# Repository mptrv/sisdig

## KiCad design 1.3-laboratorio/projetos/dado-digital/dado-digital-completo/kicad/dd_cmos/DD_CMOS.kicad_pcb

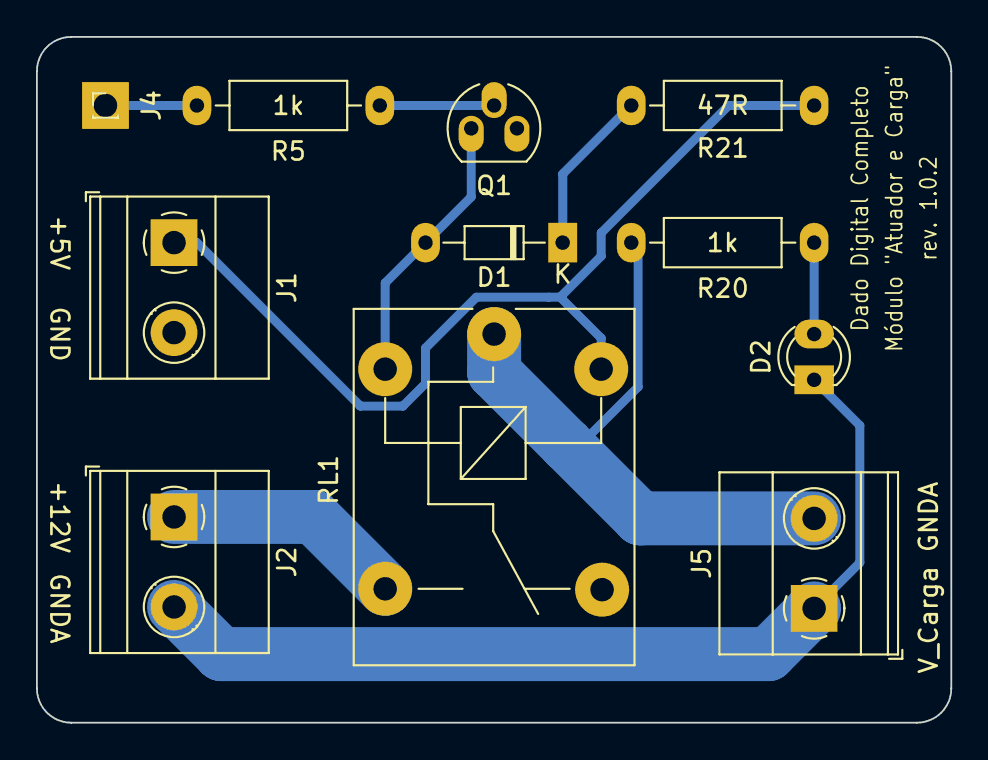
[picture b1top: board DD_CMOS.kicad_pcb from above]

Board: 2 copper layers, 50.8 x 38.1 mm, 11 parts (0 on the bottom side), 10 nets.

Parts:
D1: 1N4148; D_DO-34_SOD68_P7.62mm_Horizontal
D2: Verde; LED_D3.0mm
J1, J2, J5: Conn_01x02; TerminalBlock_Phoenix_MKDS-1,5-2_1x02_P5.00mm_Horizontal
J4: Conn_01x01; PinHeader_1x01_P1.00mm_Vertical
Q1: BC547; TO-92_HandSolder
R5, R20: 1k; R_Axial_DIN0207_L6.3mm_D2.5mm_P10.16mm_Horizontal
R21: 47R; R_Axial_DIN0207_L6.3mm_D2.5mm_P10.16mm_Horizontal
RL1: HF3FA/005-ZSTF; Relay_SPDT_SANYOU_SRD_Series_Form_C

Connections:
+12V: J2.1, RL1.14
Earth: D2.1, J2.2, J5.1
GND: J1.2, Q1.3
unnamed: D1.1, R21.2
unnamed: D1.2, Q1.1, RL1.A2
unnamed: D2.2, R20.2
unnamed: J4.1, R5.1
unnamed: J5.2, R20.1, RL1.11
unnamed: Q1.2, R5.2
VDD: J1.1, R21.1, RL1.A1

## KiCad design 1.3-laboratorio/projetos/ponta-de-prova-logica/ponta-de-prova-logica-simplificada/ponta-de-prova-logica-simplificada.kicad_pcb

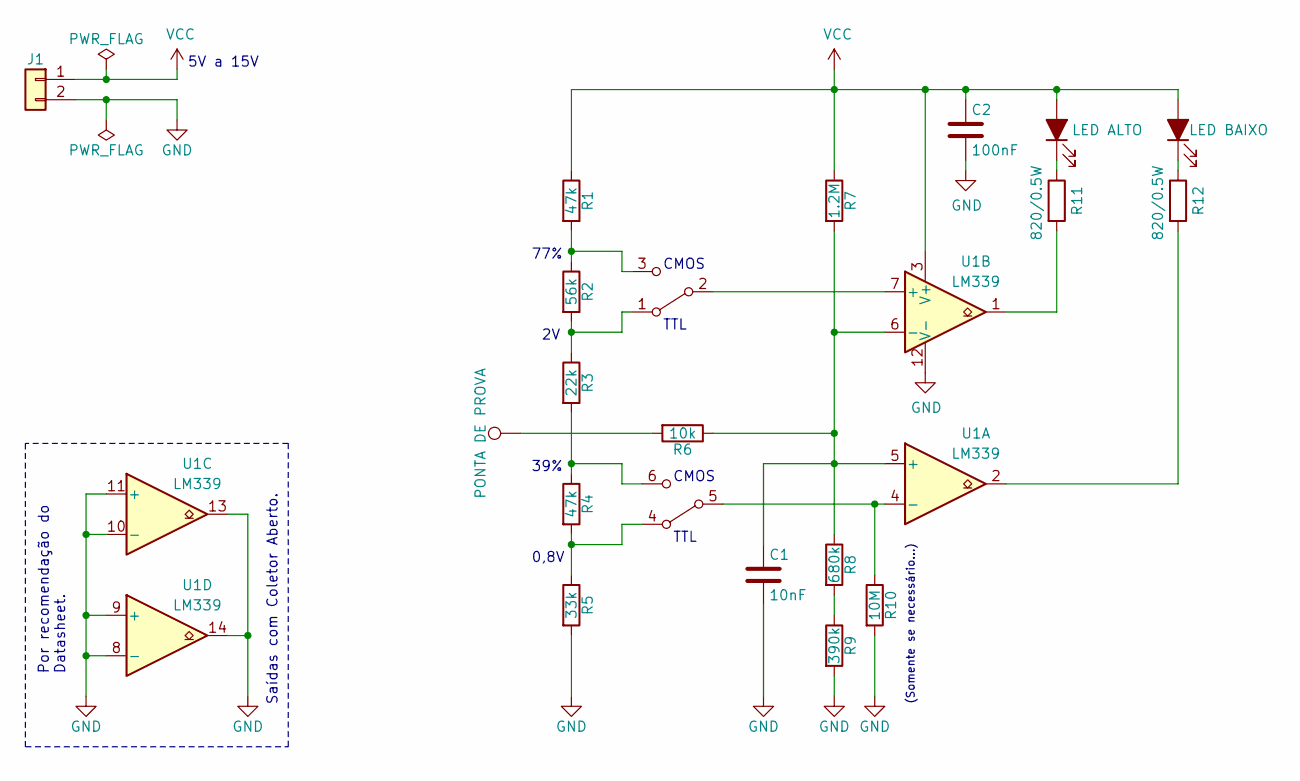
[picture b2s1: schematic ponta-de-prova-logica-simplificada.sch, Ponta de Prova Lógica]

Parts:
C1: 10nF; C_Disc_D5.0mm_W2.5mm_P5.00mm
C2: 100nF; C_Disc_D5.0mm_W2.5mm_P5.00mm
D1: LED ALTO; LED_D3.0mm
D2: LED BAIXO; LED_D3.0mm
J1: Conn_01x02; TerminalBlock_Altech_AK300-2_P5.00mm
J2: PONTA DE PROVA; SolderWirePad_1x01_Drill0.8mm
R1, R4: 47k; R_Axial_DIN0207_L6.3mm_D2.5mm_P7.62mm_Horizontal
R2: 56k; R_Axial_DIN0207_L6.3mm_D2.5mm_P7.62mm_Horizontal
R3: 22k; R_Axial_DIN0207_L6.3mm_D2.5mm_P7.62mm_Horizontal
R5: 33k; R_Axial_DIN0207_L6.3mm_D2.5mm_P7.62mm_Horizontal
R6: 10k; R_Axial_DIN0207_L6.3mm_D2.5mm_P7.62mm_Horizontal
R7: 1.2M; R_Axial_DIN0207_L6.3mm_D2.5mm_P7.62mm_Horizontal
R8: 680k; R_Axial_DIN0207_L6.3mm_D2.5mm_P7.62mm_Horizontal
R9: 390k; R_Axial_DIN0207_L6.3mm_D2.5mm_P7.62mm_Horizontal
R10: 10M; R_Axial_DIN0207_L6.3mm_D2.5mm_P7.62mm_Horizontal
R11, R12: 820/0.5W; R_Axial_DIN0207_L6.3mm_D2.5mm_P7.62mm_Horizontal
TTL1: SW_DPDT_x2; SW_CuK_JS202011CQN_DPDT_Straight
U1: LM339; DIP-14_W7.62mm_Socket_LongPads

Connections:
GND: C1.2, C2.2, J1.2, R5.2, R9.2, R10.2, U1.8 (-), U1.9 (+), U1.10 (-), U1.11 (+), U1.12 (V-), U1.13, U1.14
unnamed: C1.1, R6.1, R7.2, R8.1, U1.5 (+), U1.6 (-)
unnamed: D1.1 (K), R11.1
unnamed: D2.1 (K), R12.1
unnamed: J2.1, R6.2
unnamed 5: R1.2, R2.1, TTL1.3 (C); also elsewhere on the board
unnamed 6: R2.2, R3.1, TTL1.1 (A); also elsewhere on the board
unnamed 7: R3.2, R4.1, TTL1.6 (C); also elsewhere on the board
unnamed 8: R4.2, R5.1, TTL1.4 (A); also elsewhere on the board
unnamed: R8.2, R9.1
unnamed 10: R10.1, TTL1.5 (B), U1.4 (-); also elsewhere on the board
unnamed: R11.2, U1.1
unnamed: R12.2, U1.2
unnamed 13: TTL1.2 (B), U1.7 (+); also elsewhere on the board
VCC: C2.1, D1.2 (A), D2.2 (A), J1.1, R1.1, R7.1, U1.3 (V+)

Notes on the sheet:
0,8V
39%
77%
CMOS
TTL
Saídas com Coletor Aberto.
Por recomendação do Datasheet.
(Somente se necessário...)
5V a 15V

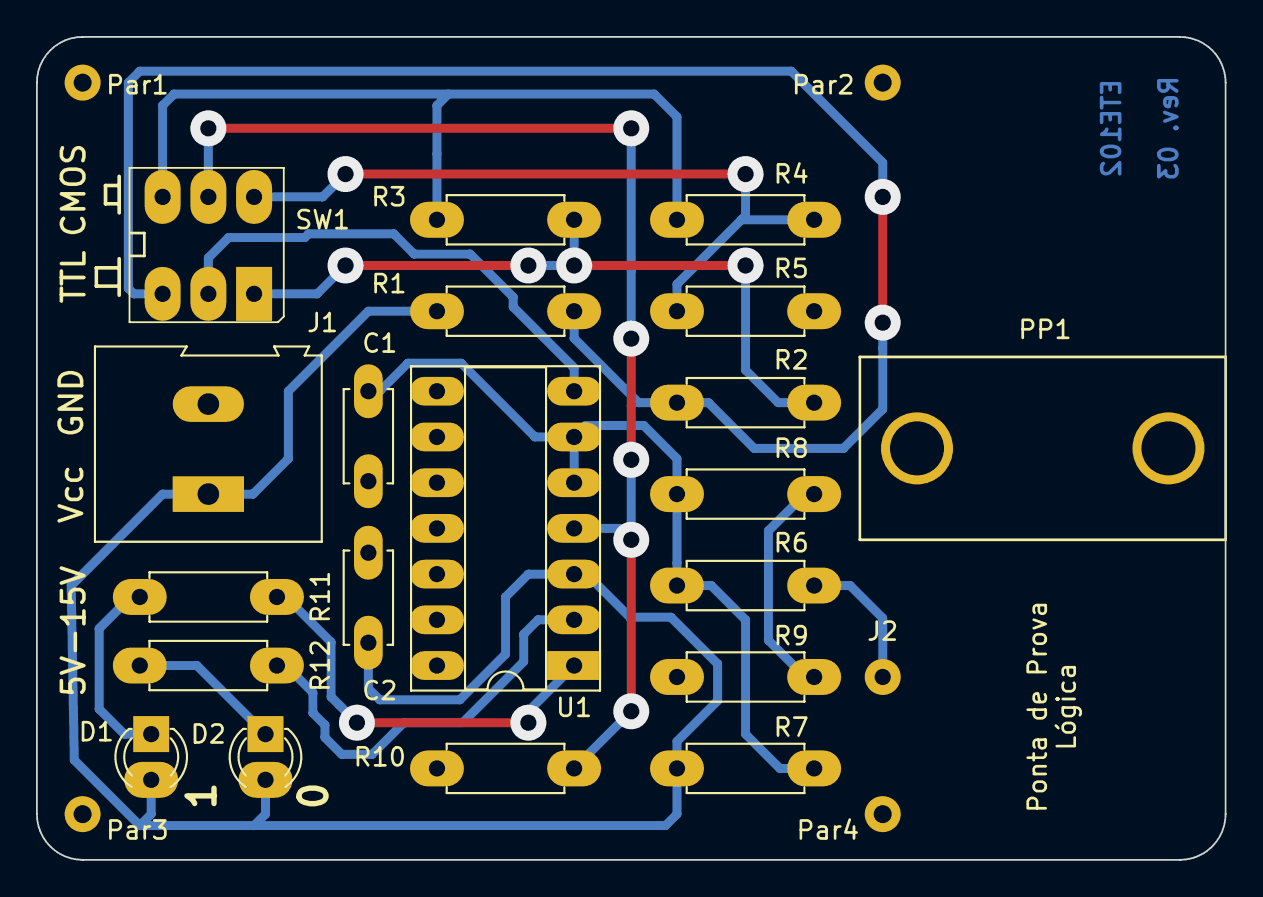
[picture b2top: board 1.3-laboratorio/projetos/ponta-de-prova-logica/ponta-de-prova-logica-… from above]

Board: 2 copper layers, 66.0 x 45.7 mm, 25 parts (0 on the bottom side), 15 nets.

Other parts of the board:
PP1: ponta-de-prova-fixacao-20mm-x-10mm-x-10mm
Par1, Par2, Par3, Par4: MountingHole_1mm_M1_DIN965_Pad; MountingHole_2.2mm_M2_DIN965_Pad
SW1: SW_DPDT_x2; Switch_Slide_JS202011SCQN

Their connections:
unnamed 5: SW1.3; also elsewhere on the board
unnamed 6: SW1.1; also elsewhere on the board
unnamed 7: SW1.6; also elsewhere on the board
unnamed 8: SW1.4; also elsewhere on the board
unnamed 10: SW1.5; also elsewhere on the board
unnamed 13: SW1.2; also elsewhere on the board

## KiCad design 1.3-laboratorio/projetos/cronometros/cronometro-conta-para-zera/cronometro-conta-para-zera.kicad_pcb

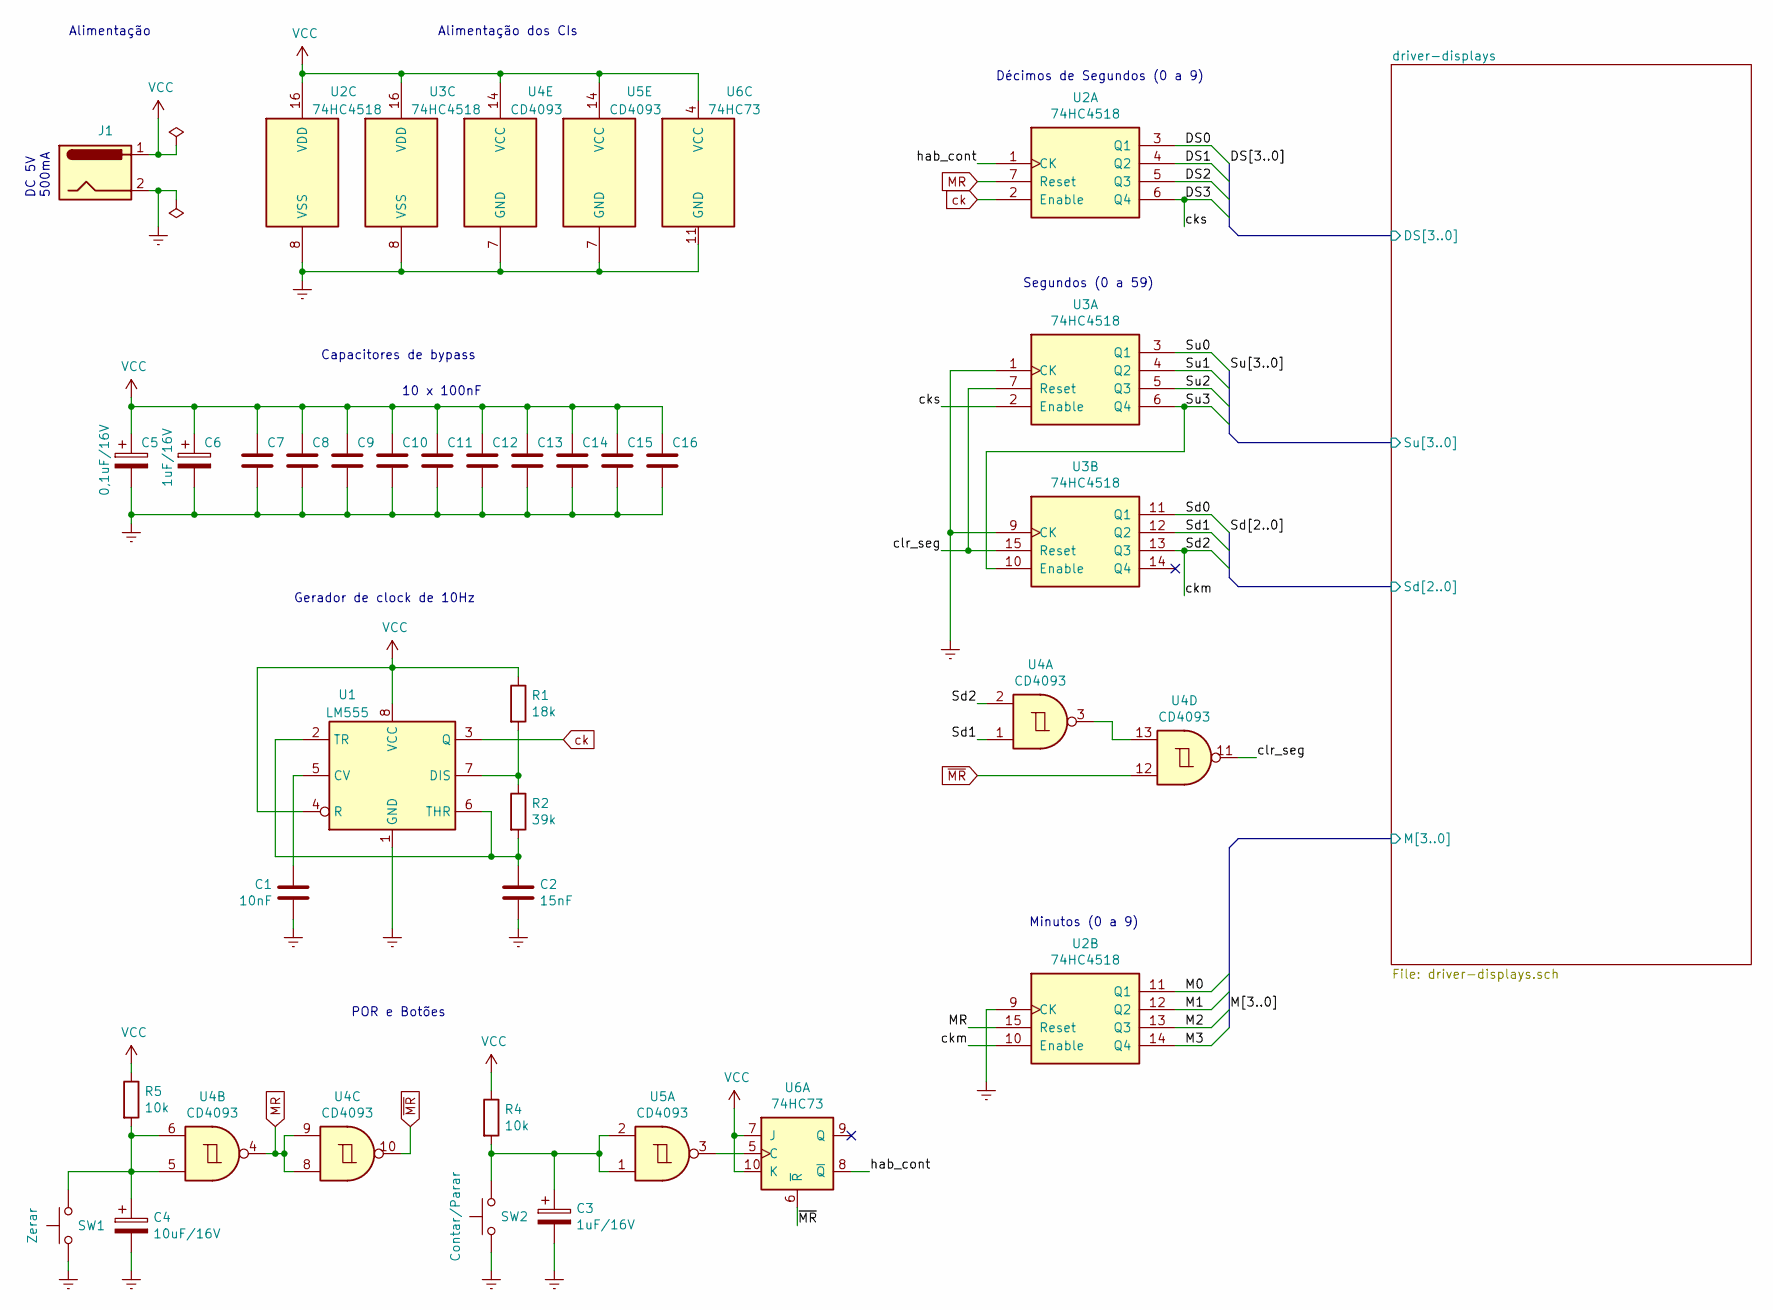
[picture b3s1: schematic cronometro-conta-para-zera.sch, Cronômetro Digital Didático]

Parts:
C1: 10nF
C2: 15nF
C3, C6: 1uF/16V
C4: 10uF/16V
C5: 0,1uF/16V
C7, C8, C9, C10, C11, C12, C13, C14, C15, C16: 100nF
J1: Barrel_Jack_Switch; BarrelJack_CUI_PJ-063AH_Horizontal
R1: 18k
R2: 39k
R4, R5: 10k
SW1, SW2: SW_Push
U1: LM555; DIP-8_W7.62mm
U2, U3: 74HC4518
U4, U5: CD4093
U6: 74HC73

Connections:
/DS0: U2.3 (Q1); also elsewhere on the board
/DS1: U2.4 (Q2); also elsewhere on the board
/DS2: U2.5 (Q3); also elsewhere on the board
/M0: U3.11 (Q1); also elsewhere on the board
/M3: U3.14 (Q4); also elsewhere on the board
/Sd0: U3.3 (Q1); also elsewhere on the board
/Su0: U2.11 (Q1); also elsewhere on the board
/Su1: U2.12 (Q2); also elsewhere on the board
/Su2: U2.13 (Q3); also elsewhere on the board
/hab_cont: U2.1 (CK), U6.8 (~Q)
Earth: C1.2, C2.2, C3.2, C4.2, C5.2, C6.2, C7.2, C8.2, C9.2, C10.2, C11.2, C12.2, C13.2, C14.2, C15.2, C16.2, J1.2, SW1.1, SW2.1, U1.1 (GND), U2.8 (VSS), U2.9 (CK), U3.1 (CK), U3.8 (VSS), U3.9 (CK), U4.7 (GND), U5.7 (GND), U6.11 (GND); also elsewhere on the board
unnamed: C1.1, U1.5 (CV)
unnamed: C2.1, R2.2, U1.2 (TR), U1.6 (THR)
unnamed: C3.1, R4.2, SW2.2, U5.1, U5.2
unnamed: C4.1, R5.2, SW1.2, U4.5, U4.6
unnamed: R1.2, R2.1, U1.7 (DIS)
unnamed: U4.3, U4.13
unnamed: U5.3, U6.5 (C)
VCC: C5.1, C6.1, C7.1, C8.1, C9.1, C10.1, C11.1, C12.1, C13.1, C14.1, C15.1, C16.1, J1.1, R1.1, R4.1, R5.1, U1.4 (R), U1.8 (VCC), U2.16 (VDD), U3.16 (VDD), U4.14 (VCC), U5.14 (VCC), U6.4 (VCC), U6.7 (J), U6.10 (K); also elsewhere on the board
ck: U1.3 (Q), U2.2 (Enable)
~MR: U4.10, U4.12, U6.6 (~R)

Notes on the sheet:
DC 5V 500mA
Gerador de clock de 10Hz
Décimos de Segundos (0 a 9)
Segundos (0 a 59)
Minutos (0 a 9)
POR e Botões
Capacitores de bypass
Alimentação dos CIs
10 x 100nF
Alimentação

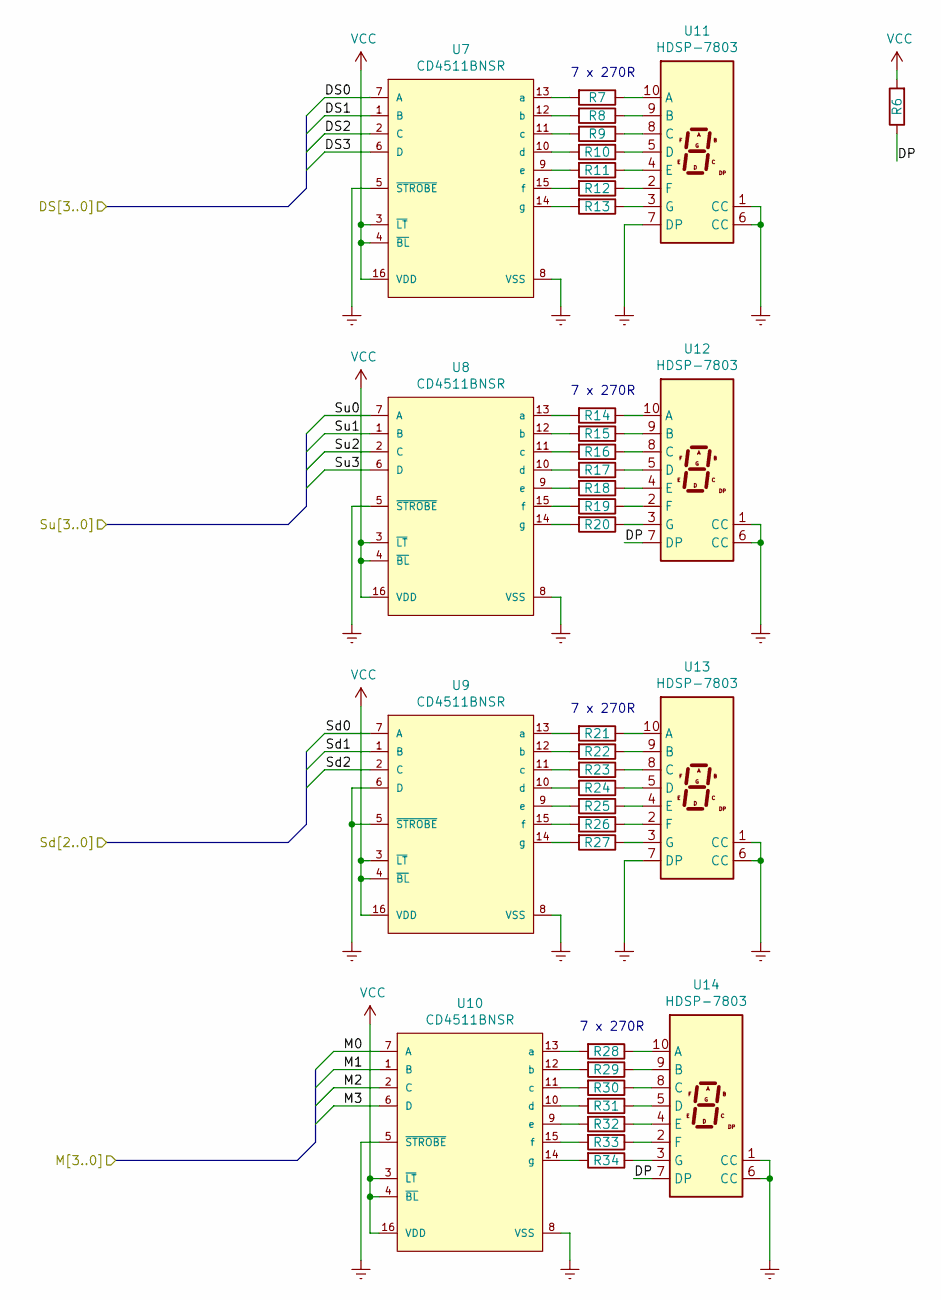
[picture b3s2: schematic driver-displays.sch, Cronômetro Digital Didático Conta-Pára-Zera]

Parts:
R6, R7, R8, R9, R10, R11, R12, R13, R14, R15, R16, R17, R18, R19, R20, R21, R22, R23, R24, R25, R26, R27, R28, R29, R30, R31, R32, R33, R34: 270R; R_Axial_DIN0204_L3.6mm_D1.6mm_P7.62mm_Horizontal
U7, U8, U9, U10: CD4511BNSR; DIP-16_W7.62mm_Socket_LongPads; Rating Military
U11, U12, U13, U14: HDSP-7803; HDSP-7801

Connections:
/DS0: U7.7 (A); also elsewhere on the board
/DS1: U7.1 (B); also elsewhere on the board
/DS2: U7.2 (C); also elsewhere on the board
/M0: U10.7 (A); also elsewhere on the board
/M3: U10.6 (D); also elsewhere on the board
/Sd0: U9.7 (A); also elsewhere on the board
/Su0: U8.7 (A); also elsewhere on the board
/Su1: U8.1 (B); also elsewhere on the board
/Su2: U8.2 (C); also elsewhere on the board
/driver-displays/DP: R6.1, U12.7 (DP), U14.7 (DP)
Earth: U7.5 (~STROBE~), U7.8 (VSS), U8.5 (~STROBE~), U8.8 (VSS), U9.5 (~STROBE~), U9.6 (D), U9.8 (VSS), U10.5 (~STROBE~), U10.8 (VSS), U11.1 (CC), U11.6 (CC), U11.7 (DP), U12.1 (CC), U12.6 (CC), U13.1 (CC), U13.6 (CC), U13.7 (DP), U14.1 (CC), U14.6 (CC); also elsewhere on the board
unnamed: R7.1, U11.10 (A)
unnamed: R7.2, U7.13 (a)
unnamed: R8.1, U11.9 (B)
unnamed: R8.2, U7.12 (b)
unnamed: R9.1, U11.8 (C)
unnamed: R9.2, U7.11 (c)
unnamed: R10.1, U11.5 (D)
unnamed: R10.2, U7.10 (d)
unnamed: R11.1, U11.4 (E)
unnamed: R11.2, U7.9 (e)
unnamed: R12.1, U11.2 (F)
unnamed: R12.2, U7.15 (f)
unnamed: R13.1, U11.3 (G)
unnamed: R13.2, U7.14 (g)
unnamed: R14.1, U12.10 (A)
unnamed: R14.2, U8.13 (a)
unnamed: R15.1, U12.9 (B)
unnamed: R15.2, U8.12 (b)
unnamed: R16.1, U12.8 (C)
unnamed: R16.2, U8.11 (c)
unnamed: R17.1, U12.5 (D)
unnamed: R17.2, U8.10 (d)
unnamed: R18.1, U12.4 (E)
unnamed: R18.2, U8.9 (e)
unnamed: R19.1, U12.2 (F)
unnamed: R19.2, U8.15 (f)
unnamed: R20.1, U12.3 (G)
unnamed: R20.2, U8.14 (g)
unnamed: R21.1, U13.10 (A)
unnamed: R21.2, U9.13 (a)
unnamed: R22.1, U13.9 (B)
unnamed: R22.2, U9.12 (b)
unnamed: R23.1, U13.8 (C)
unnamed: R23.2, U9.11 (c)
unnamed: R24.1, U13.5 (D)
unnamed: R24.2, U9.10 (d)
unnamed: R25.1, U13.4 (E)
unnamed: R25.2, U9.9 (e)
unnamed: R26.1, U13.2 (F)
unnamed: R26.2, U9.15 (f)
unnamed: R27.1, U13.3 (G)
unnamed: R27.2, U9.14 (g)
unnamed: R28.1, U14.10 (A)
unnamed: R28.2, U10.13 (a)
unnamed: R29.1, U14.9 (B)
unnamed: R29.2, U10.12 (b)
unnamed: R30.1, U14.8 (C)
unnamed: R30.2, U10.11 (c)
unnamed: R31.1, U14.5 (D)
unnamed: R31.2, U10.10 (d)
unnamed: R32.1, U14.4 (E)
unnamed: R32.2, U10.9 (e)
unnamed: R33.1, U14.2 (F)
unnamed: R33.2, U10.15 (f)
unnamed: R34.1, U14.3 (G)
unnamed: R34.2, U10.14 (g)
VCC: R6.2, U7.3 (~LT~), U7.4 (~BL~), U7.16 (VDD), U8.3 (~LT~), U8.4 (~BL~), U8.16 (VDD), U9.3 (~LT~), U9.4 (~BL~), U9.16 (VDD), U10.3 (~LT~), U10.4 (~BL~), U10.16 (VDD); also elsewhere on the board

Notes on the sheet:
7 x 270R

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
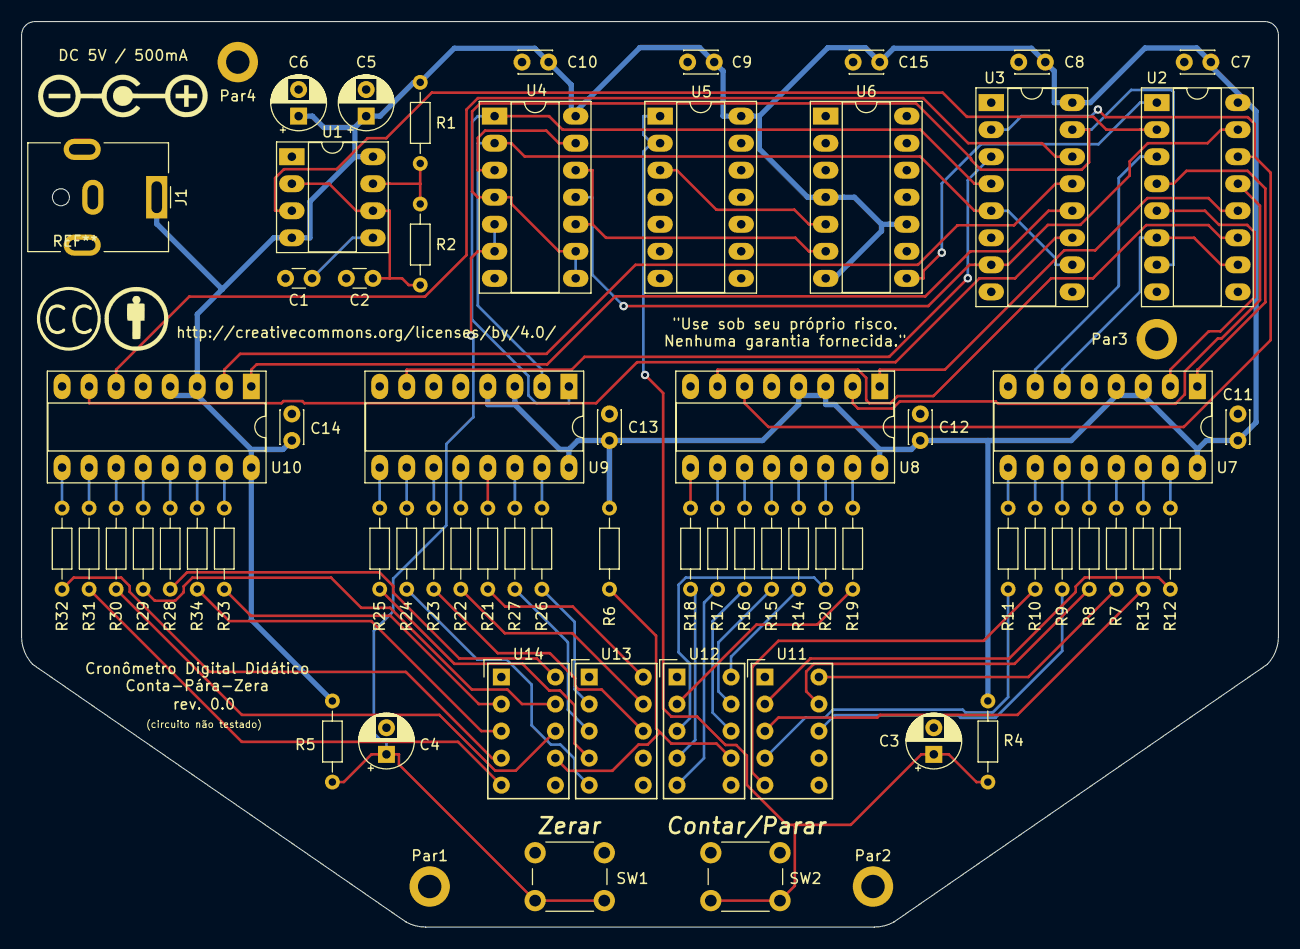
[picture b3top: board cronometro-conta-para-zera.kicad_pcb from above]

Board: 2 copper layers, 118.1 x 85.1 mm, 69 parts (0 on the bottom side), 86 nets.

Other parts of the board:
Par1, Par2, Par3, Par4: MountingHole_2.2mm_M2_DIN965_Pad

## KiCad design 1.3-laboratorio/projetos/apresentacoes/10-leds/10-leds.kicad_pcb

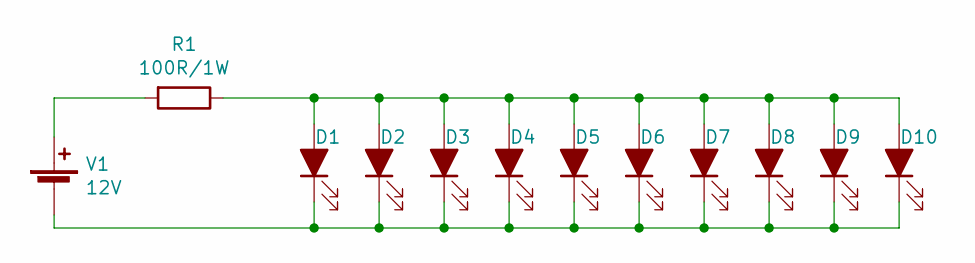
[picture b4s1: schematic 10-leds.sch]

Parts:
D1, D2, D3, D4, D5, D6, D7, D8, D9, D10: LED_ALT; LED_D5.0mm
R1: 100R/1W; R_Axial_DIN0204_L3.6mm_D1.6mm_P5.08mm_Horizontal
V1: 12V; TerminalBlock_Phoenix_MKDS-1,5-2-5.08_1x02_P5.08mm_Horizont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

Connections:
unnamed: D1.1 (K), D2.1 (K), D3.1 (K), D4.1 (K), D5.1 (K), D6.1 (K), D7.1 (K), D8.1 (K), D9.1 (K), D10.1 (K), V1.2 (-)
unnamed: D1.2 (A), D2.2 (A), D3.2 (A), D4.2 (A), D5.2 (A), D6.2 (A), D7.2 (A), D8.2 (A), D9.2 (A), D10.2 (A), R1.1
unnamed: R1.2, V1.1 (+)

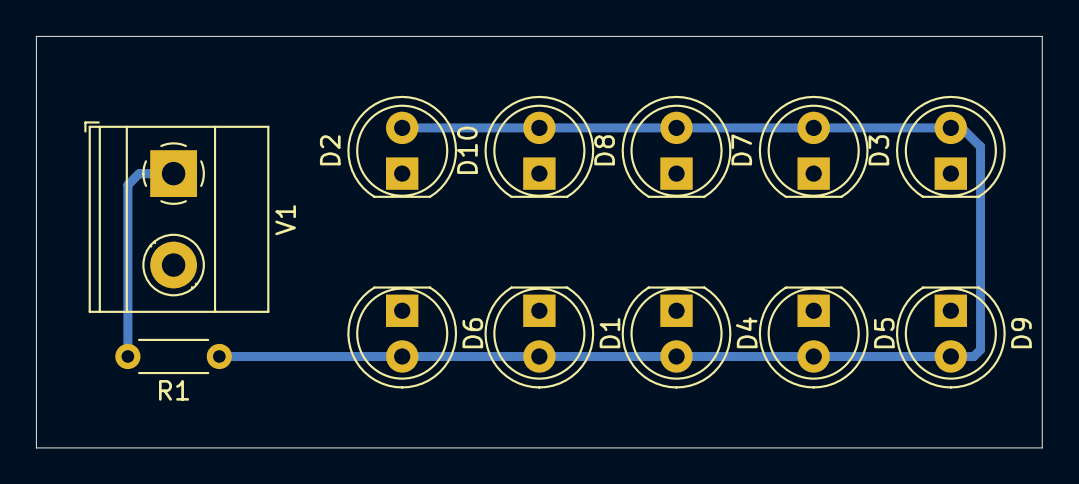
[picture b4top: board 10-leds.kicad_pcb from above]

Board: 2 copper layers, 55.9 x 22.9 mm, 12 parts (0 on the bottom side), 3 nets.

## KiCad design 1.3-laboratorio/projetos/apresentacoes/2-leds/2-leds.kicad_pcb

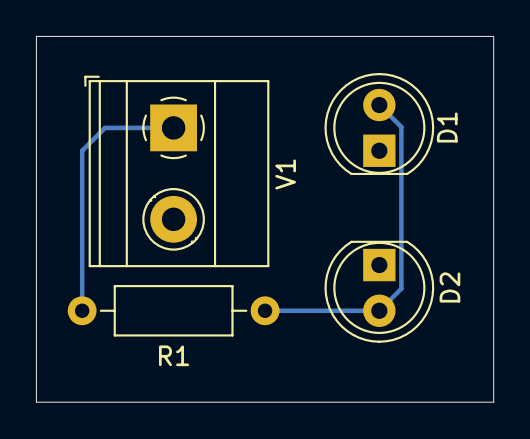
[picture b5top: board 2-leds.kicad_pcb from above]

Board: 2 copper layers, 25.4 x 20.3 mm, 4 parts (0 on the bottom side), 3 nets.

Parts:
D1, D2: LED_ALT; LED_D5.0mm
R1: 470R/0,5W; R_Axial_DIN0207_L6.3mm_D2.5mm_P10.16mm_Horizontal
V1: 12V; TerminalBlock_Phoenix_MKDS-1,5-2-5.08_1x02_P5.08mm_Horizont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

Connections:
/gnd: D1.1, D2.1, V1.2
unnamed: D1.2, D2.2, R1.2
unnamed: R1.1, V1.1

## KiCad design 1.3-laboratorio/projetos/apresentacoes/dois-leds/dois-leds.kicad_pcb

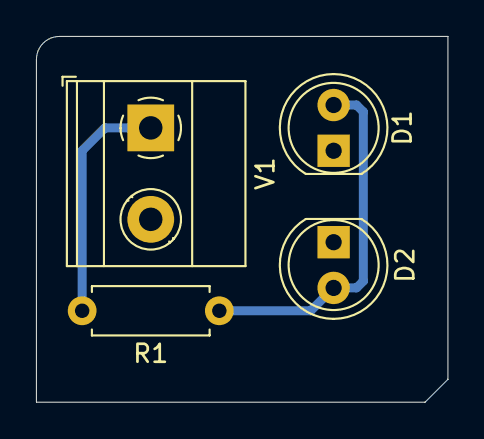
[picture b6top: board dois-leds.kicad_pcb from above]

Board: 2 copper layers, 22.9 x 20.3 mm, 4 parts (0 on the bottom side), 3 nets.

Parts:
D1, D2: LED_ALT; LED_D5.0mm
R1: 470R/0,5W; R_Axial_DIN0207_L6.3mm_D2.5mm_P7.62mm_Horizontal
V1: 12V; TerminalBlock_Phoenix_MKDS-1,5-2-5.08_1x02_P5.08mm_Horizont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

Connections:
/gnd: D1.1, D2.1, V1.2
unnamed: D1.2, D2.2, R1.1
unnamed: R1.2, V1.1

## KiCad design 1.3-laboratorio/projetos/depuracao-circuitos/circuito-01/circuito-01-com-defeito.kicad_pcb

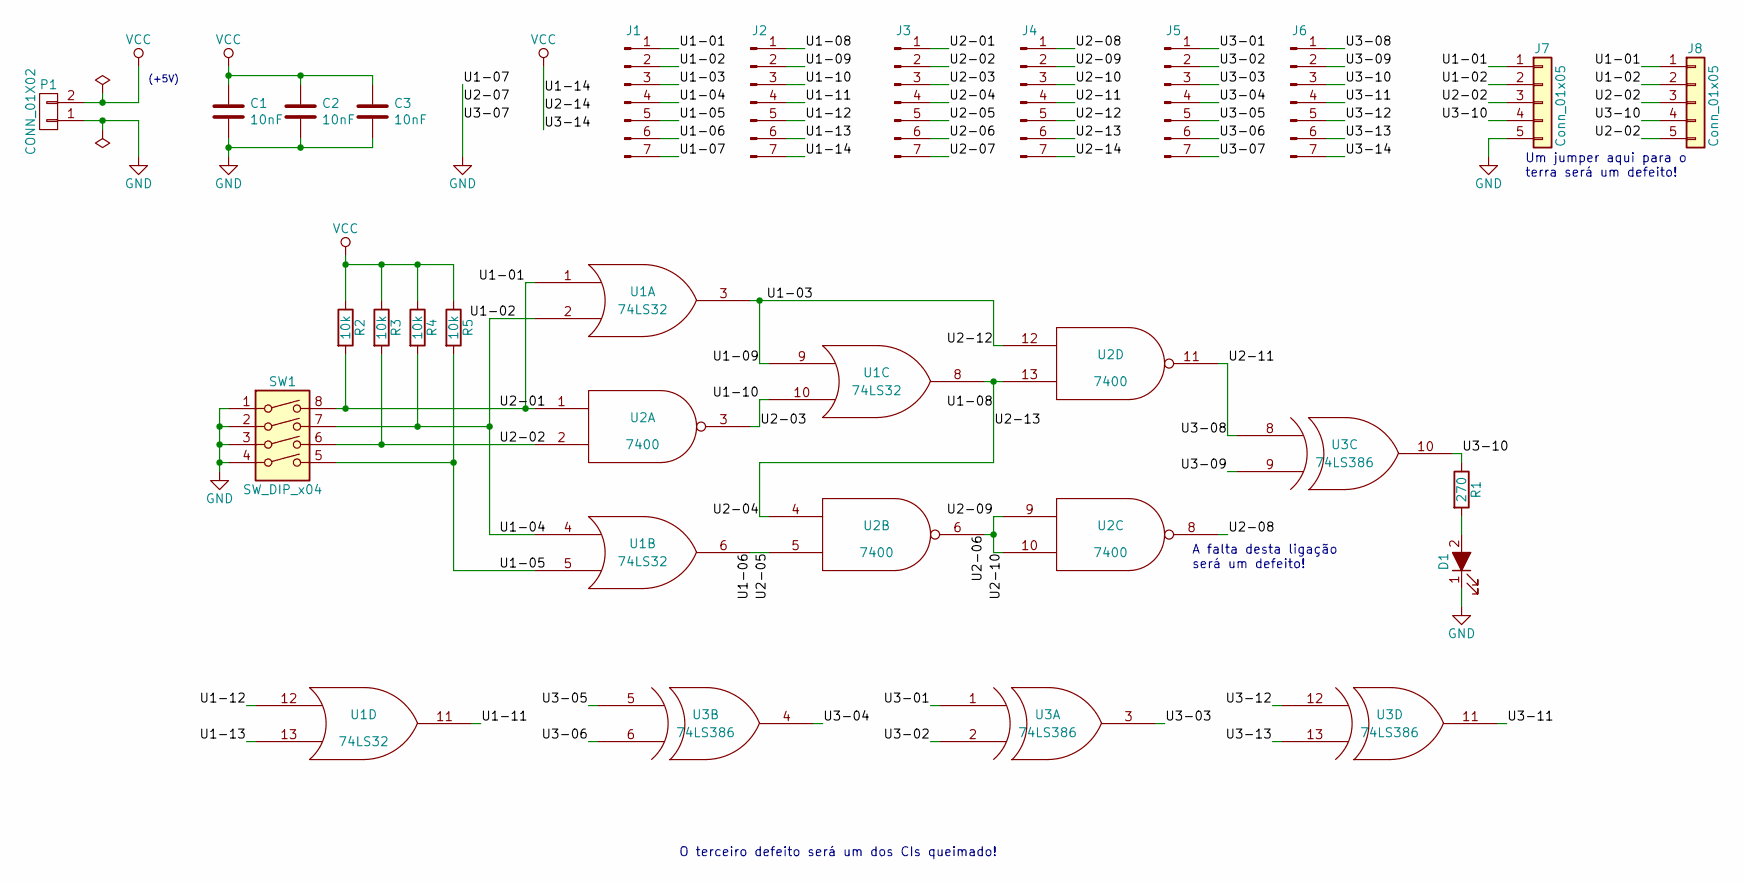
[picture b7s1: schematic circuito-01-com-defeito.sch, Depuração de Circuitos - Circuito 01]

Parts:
C1, C2, C3: 10nF; C_Disc_D5.0mm_W2.5mm_P5.00mm
D1: LED_ALT; LED_D5.0mm
J1, J2, J3, J4, J5, J6: Conn_01x07_Male; PinHeader_1x07_P2.54mm_Vertical
J7, J8: Conn_01x05; PinSocket_1x05_P2.54mm_Vertical
P1: CONN_01X02; Altech_AK300_1x02_P5.00mm_45-Degree
R1: 270; R_Axial_DIN0207_L6.3mm_D2.5mm_P10.16mm_Horizontal
R2, R3, R4, R5: 10k; R_Axial_DIN0207_L6.3mm_D2.5mm_P10.16mm_Horizontal
SW1: SW_DIP_x04; SW_DIP_SPSTx04_Slide_9.78x12.34mm_W7.62mm_P2.54mm
U1: 74LS32; DIP-14_W7.62mm_Socket_LongPads
U2: 7400; DIP-14_W7.62mm_Socket_LongPads
U3: 74LS386; DIP-14_W7.62mm_Socket_LongPads

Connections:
/U1-01: J1.1, J3.1, J7.1, J8.1, R2.2, SW1.8, U1.1, U2.1
/U1-02: J1.2, J1.4, J7.2, J8.2, R4.2, SW1.7, U1.2, U1.4
/U1-03: J1.3, J2.2, J4.5, U1.3, U1.9, U2.12
/U1-05: J1.5, R5.2, SW1.5, U1.5
/U1-06: J1.6, J3.5, U1.6, U2.5
/U1-08: J2.1, J3.4, J4.6, U1.8, U2.4, U2.13
/U1-10: J2.3, J3.3, U1.10, U2.3
/U1-11: J2.4, U1.11
/U1-12: J2.5, U1.12
/U1-13: J2.6, U1.13
/U2-02: J3.2, J7.3, J8.3, J8.5, R3.2, SW1.6, U2.2
/U2-06: J3.6, J4.2, J4.3, U2.6, U2.9, U2.10
/U2-08: J4.1, U2.8
/U2-11: J4.4, J6.1, U2.11, U3.8
/U3-01: J5.1, U3.1
/U3-02: J5.2, U3.2
/U3-03: J5.3, U3.3
/U3-04: J5.4, U3.4
/U3-05: J5.5, U3.5
/U3-06: J5.6, U3.6
/U3-09: J6.2, U3.9
/U3-10: J6.3, J7.4, J8.4, R1.1, U3.10
/U3-11: J6.4, U3.11
/U3-12: J6.5, U3.12
/U3-13: J6.6, U3.13
GND: C1.2, C2.2, C3.2, D1.1 (K), J1.7, J3.7, J5.7, J7.5, P1.1, SW1.1, SW1.2, SW1.3, SW1.4, U1.7 (GND), U2.7 (GND), U3.7 (GND)
unnamed: D1.2 (A), R1.2
VCC: C1.1, C2.1, C3.1, J2.7, J4.7, J6.7, P1.2, R2.1, R3.1, R4.1, R5.1, U1.14 (VCC), U2.14 (VCC), U3.14 (VCC)

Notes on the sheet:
(+5V)
Um jumper aqui para o terra será um defeito!
A falta desta ligação será um defeito!
O terceiro defeito será um dos CIs queimado!

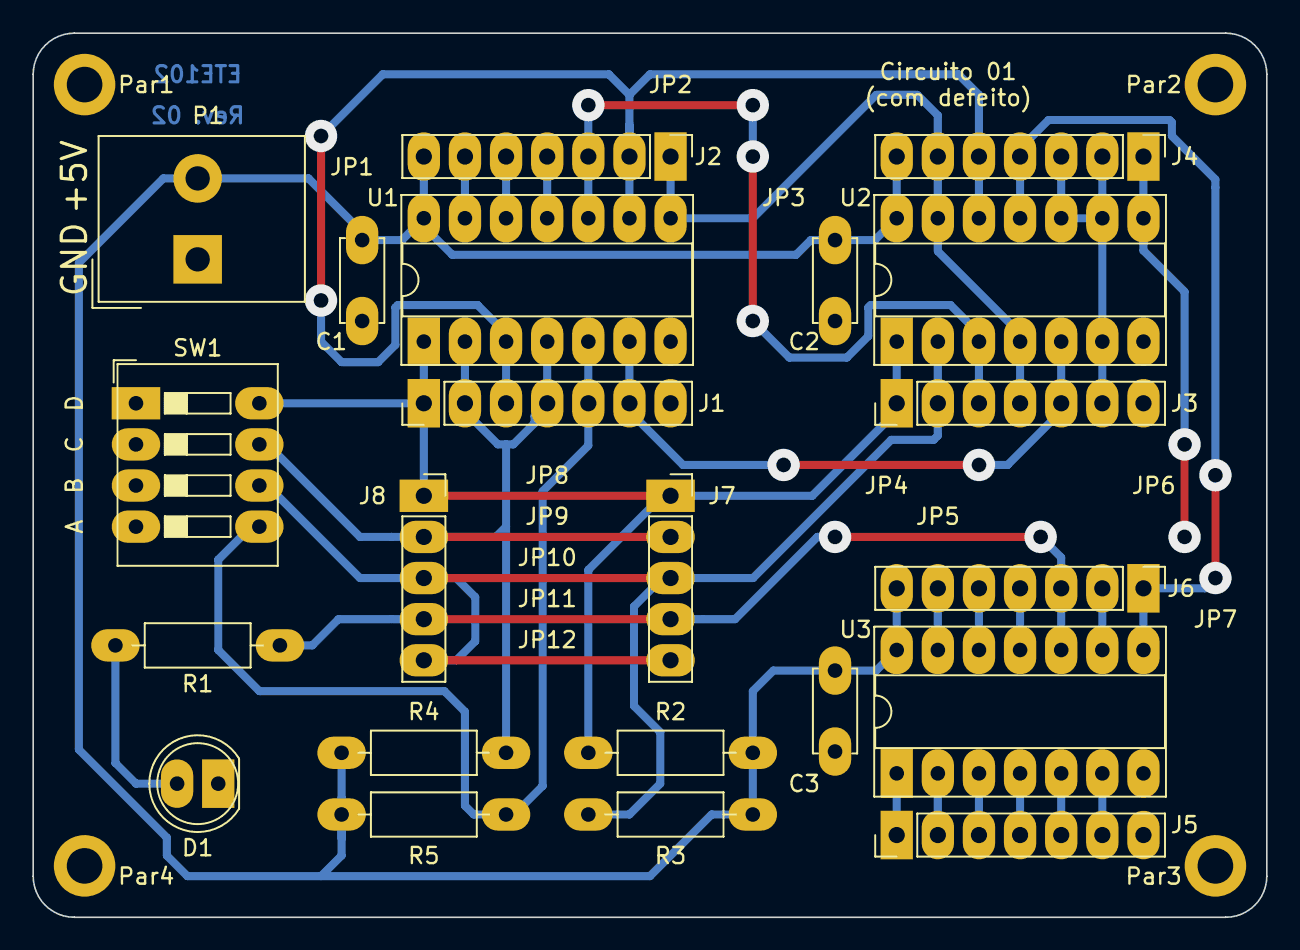
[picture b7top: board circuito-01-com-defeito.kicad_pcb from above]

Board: 2 copper layers, 76.2 x 54.6 mm, 26 parts (0 on the bottom side), 28 nets.

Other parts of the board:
Par1, Par2, Par3, Par4: MountingHole_2.2mm_M2_ISO14580_Pad

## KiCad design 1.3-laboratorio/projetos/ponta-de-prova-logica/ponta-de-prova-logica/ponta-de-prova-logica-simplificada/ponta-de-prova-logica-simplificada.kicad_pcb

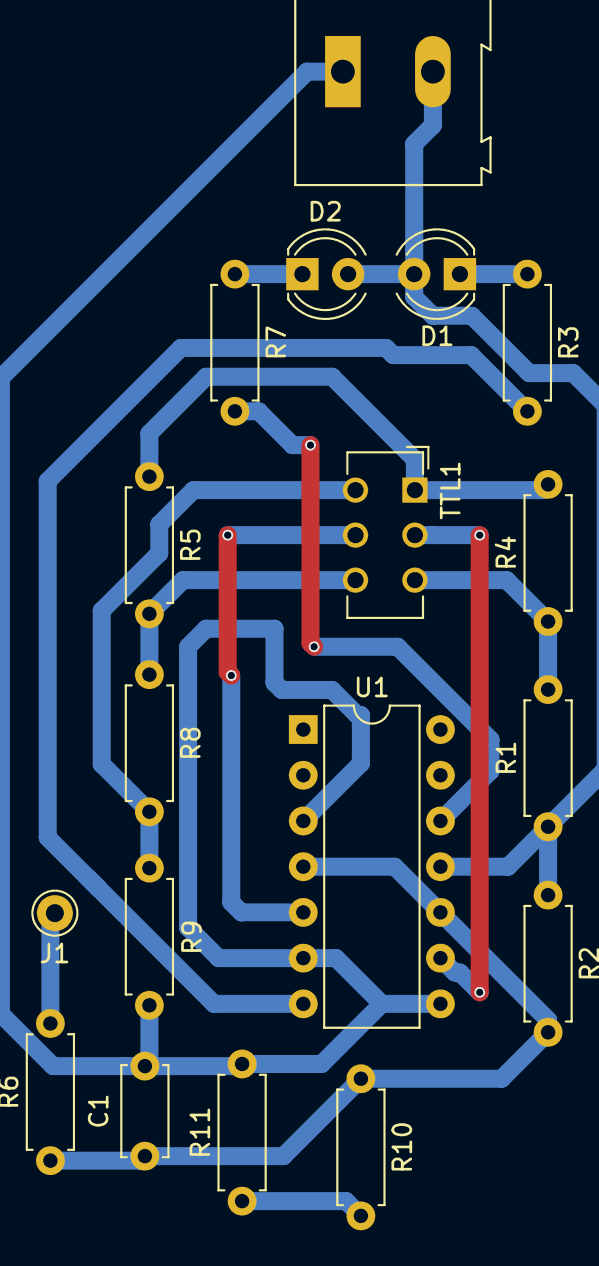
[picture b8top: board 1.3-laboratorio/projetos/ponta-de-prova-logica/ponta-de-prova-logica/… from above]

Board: 2 copper layers, 18 parts (0 on the bottom side), 15 nets.

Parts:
C1: 10nF; C_Disc_D5.0mm_W2.5mm_P5.00mm
D1: LED HIGH; LED_D4.0mm
D2: LED LOW; LED_D4.0mm
J1: TEST PROBE; Pin_d1.0mm_L10.0mm
J2: Conn_01x02; TerminalBlock_Altech_AK300-2_P5.00mm
R1, R8: 47k; R_Axial_DIN0207_L6.3mm_D2.5mm_P7.62mm_Horizontal
R2: 1.2M; R_Axial_DIN0207_L6.3mm_D2.5mm_P7.62mm_Horizontal
R3, R7: 560/0.5W; R_Axial_DIN0207_L6.3mm_D2.5mm_P7.62mm_Horizontal
R4: 56k; R_Axial_DIN0207_L6.3mm_D2.5mm_P7.62mm_Horizontal
R5: 22k; R_Axial_DIN0207_L6.3mm_D2.5mm_P7.62mm_Horizontal
R6: 10k; R_Axial_DIN0207_L6.3mm_D2.5mm_P7.62mm_Horizontal
R9: 33k; R_Axial_DIN0207_L6.3mm_D2.5mm_P7.62mm_Horizontal
R10: 680k; R_Axial_DIN0207_L6.3mm_D2.5mm_P7.62mm_Horizontal
R11: 390k; R_Axial_DIN0207_L6.3mm_D2.5mm_P7.62mm_Horizontal
TTL1: SW_DPDT_x2; SW_CuK_JS202011AQN_DPDT_Angled
U1: LM319; DIP-14_W7.62mm

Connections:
+5V: D1.2, D2.2, J2.2, R1.1, R2.1, U1.11
GND: C1.2, J2.1, R9.2, R11.2, U1.3, U1.6, U1.8
unnamed: C1.1, R2.2, R6.1, R10.1, U1.4, U1.10
unnamed: D1.1, R3.1
unnamed: D2.1, R7.1
unnamed: J1.1, R6.2
unnamed: R1.2, R4.1, TTL1.3
unnamed: R3.2, U1.7
unnamed: R4.2, R5.1, TTL1.1
unnamed: R5.2, R8.1, TTL1.6
unnamed: R7.2, U1.12
unnamed: R8.2, R9.1, TTL1.4
unnamed: R10.2, R11.1
unnamed: TTL1.2, U1.9
unnamed: TTL1.5, U1.5

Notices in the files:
1.3-laboratorio/projetos/cronometros/cronometro-conta-para-zera/cronometro-conta-para-zera.kicad_pcb:
CC BY 4.0 (https://creativecommons.org/licenses/by/4.0/)
http://creativecommons.org/licenses/by/4.0
1.3-laboratorio/projetos/dado-digital/dado-digital-completo/kicad/dd_cmos/DD_CMOS.kicad_pcb:
CC-BY-SA 4.0
1.3-laboratorio/projetos/depuracao-circuitos/circuito-01/circuito-01-com-defeito.sch:
Licença: CC-BY-SA (http://creativecommons.org/licenses/by-sa/4.0/)
